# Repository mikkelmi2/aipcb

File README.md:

# aipcb

**A circuit board described as intent, compiled to KiCad.**

You write what the circuit *is* — in YAML. `aipcb` compiles it into real KiCad
schematics and boards, places, routes, pours, runs KiCad's own ERC and DRC on the
result, and can hand each pair to a field solver. Every problem points back at the
source line that caused it, and your KiCad edits survive the next build.

That is `examples/pcie-sata`, bundled here — a PCIe x1 card, four-port SATA, eleven
controlled-impedance pairs, four layers. Every image below is generated from it by
[`tools/make_images.py`](tools/make_images.py).

## What fifteen milestones hardened

**Deterministic compilation.** The same YAML gives byte-identical KiCad files —
rebuild unchanged and the file is not even rewritten. Every UUID is derived from
the source, which is what maps each element back to the line that asked for it.

**Verification you can trust.** ERC and DRC are run by KiCad itself, never
reimplemented, and come back as source-referenced diagnostics. Three invariants
guard the tool that produces them: `check` is a function of its source, no two
nets' copper may overlap, no simulation slice may be built with unbonded copper or
an unreachable reference plane. Each was learnt from a real defect, and
[`docs/reports/`](docs/reports/) tells the stories.

**Schematic generation.** Sheets drawn by convention from what the source already
knows — what serves what, which rails go up — proven identical to the source
netlist pin for pin, and ERC-clean.

**Manual layout is first-class.** `preserve` carries your KiCad edits across
rebuilds, `sync-placement` writes parts you moved back into the source,
`routing: manual` marks a net as yours, and the Freerouting bridge checks what
another router sends back.

## Maturity at a glance

| | | |
|---|---|---|
| Source format, compilation, `check`, schematics | **stable** | [`format.md`](docs/format.md) |
| Manual layout — preserve, `sync-placement`, `routing: manual` | **stable** | [`workflows.md`](docs/workflows.md) |
| Part placement | **basic** — shelf-packed clusters, unoptimised on purpose | [`roadmap.md`](docs/roadmap.md#placement) |
| Autorouting | **beta** — finishes this corpus, has never met a board it did not design | [`topology.md`](docs/topology.md) |
| SI simulation | **beta** — physically valid on ten of eleven links | [`m13.md`](docs/reports/m13.md) |
| Freerouting bridge | **new** — landed in M14e | [`external-routers.md`](docs/external-routers.md) |

## What beta means here

**The autorouter** finishes the corpus: `examples/pcie-sata` comes back **90 of 90
connections routed, 12 of 12 pairs coupled, 0 errors from KiCad's own DRC**, on
four layers. What it has not done is meet a board somebody else designed. The label
costs little: it **fails loudly**, naming each connection it could not finish
rather than leaving the board quietly short, and it is **optional** —
`routing: manual` and the Freerouting bridge take it out of the loop.

**SI simulation** extracts ten of the eleven flagship links physically; the
eleventh is reported unusable rather than plotted. It validates the layout you
declared, not the board a fabricator presses: it finds a pair routed too narrow, it
does not replace a test coupon, and it certifies compliance with nothing.

*Beta is a measurement, not a mood:* routing graduates once it has routed five
externally-contributed boards, passed a harder congestion stress example, and been
benchmarked against board size. The third of those is **done** — `aipcb bench`
records the whole corpus and CI diffs a subset on every change; routing cost grows
close to linearly in connections × triangulation size, and the numbers are in
[the M17 report](docs/reports/m17.md). The other two need a board this project did
not design. [The conditions in full](docs/roadmap.md#maturity-and-graduation).

## Source to fabrication, in six steps

### 1. Declare intent, not geometry

The width is *derived* from the impedance and the stackup — you never compute it:

```yaml
net_classes:
  pcie_tx:
    impedance_diff_ohm: 85    # the requirement; the trace width follows
    diff_pair_gap_mm: 0.15    # a manufacturing choice, so an input
    max_skew_mm: 0.127        # PCIe CEM r3.0 §4.7.7, for an add-in card
    reference: In1.Cu         # the plane the return current uses
```

### 2. It compiles to a schematic

### 3. Parts are placed

Mechanically-fixed parts anchor the board, everything else is placed relative to
what it serves, and the outline is checked against the card-edge footprint's own
`Edge.Cuts` rather than drawn twice.

### 4. And routed

A topological router negotiating congestion across four layers. Coupled pairs route
as one object — through the AC-coupling capacitors, across layer changes, at the
derived width.

### 5. The pairs are simulated

`aipcb simulate` slices each pair out of the routed board with its reference plane,
meshes it, runs openEMS.

The honest version of that picture: **six of the eleven pairs come back more than
10% from the impedance they declared**. That is the step doing its job: the
closed-form width says one thing, the field solver says how wrong it was.

### 6. And exported for fabrication — or for assembly

`aipcb export` writes Gerbers, drill files, a BOM and a placement file — the render
at the top of this page is KiCad's, from that output. `--assembly` adds what an
*assembler* needs on top of what a fabricator does: a bill of materials and a
centroid file in JLCPCB's or PCBWay's own columns, and a placement overlay drawn
from the centroid file itself, so the rotations can be looked at before anything is
ordered.

## You do the layout, if you want

| Mode | You do | aipcb does |
|---|---|---|
| **Full auto** | nothing | places, routes, pours, checks |
| **Hybrid** | draw the nets you care about, in KiCad | routes the rest *around* your copper, never through it, and checks all of it identically |
| **Fully manual** | all the copper | schematic, placement, pours, ERC/DRC, high-speed checks, export |

Hybrid is the one most people want. Mark a net or a whole class as yours:

```yaml
nets:
  PCIE_TXP: { class: pcie_tx, routing: manual }   # this one is mine
```

`aipcb check --json` then reports every net as `manual-routed`, `manual-pending`,
`auto-routed` or `handed-over`. `manual-pending` is the one that matters: a board
whose critical pairs are declared-and-not-yet-drawn looks finished to anything
counting unrouted connections, and this names it. Or hand the board to another
router — [Freerouting, headlessly](docs/external-routers.md).

## Quickstart

Python 3.12+ and **KiCad 9**, the backend rather than an optional extra: compiling
reads its stock libraries, and check, render and export shell out to `kicad-cli`.

```bash
git clone https://github.com/mikkelmi2/aipcb && cd aipcb
python3 -m venv .venv && .venv/bin/pip install -e .
.venv/bin/aipcb validate examples/usb-port/design.yaml
```

About 7 seconds on a warm pip cache, and out comes `ok: no problems found` with a
one-line summary. Now build it and open the result in KiCad:

```bash
.venv/bin/aipcb build examples/usb-port/design.yaml
kicad examples/usb-port/usb-port.kicad_pro
```

Then break it on purpose — change `diff_pair: USB_DP` to `USB_DPP` under
`nets: USB_DM:` — and validate again. Located, coded diagnostics rather than a
stack trace is what makes the loop work:

```
examples/usb-port/design.yaml:53:3: error[asymmetric-diff-pair]: net 'USB_DP'
names 'USB_DM' as its differential partner, but 'USB_DM' names USB_DPP
  at: nets.USB_DM.diff_pair
  hint: set `diff_pair: USB_DP` on 'USB_DM'
[... and error[unknown-diff-pair] for the net 'USB_DPP' that does not exist]

2 errors
```

`--json` gives the same thing machine-readably. [`docs/format.md`](docs/format.md)
is the reference for every key; [`docs/workflows.md`](docs/workflows.md) is how the
loop is used.

## What it does not do

**Not built.** Dense BGA escape, DDR fly-by topologies, HDI (blind and buried
vias), six or more layers, multi-sheet schematics, buses. Not "coming soon" —
absent, and a board needing them hands over rather than guesses. The class shown to
finish is the one above: small, high-speed-critical, two or four layers, and
[`docs/roadmap.md`](docs/roadmap.md) says which of the rest are wanted.

**No board from this repository has been fabricated yet.** When one has, this
paragraph will say so with pictures.

## Documentation

[`docs/README.md`](docs/README.md) is the map, and repeats the tiers above.

**This project was built milestone by milestone by AI agents, and the whole
engineering record is in the repository** — every specification, thirteen decision
records, and a delivery report per milestone measuring what actually landed. Start
at [`docs/reports/`](docs/reports/): written for someone who was not there, and
candid about what did not work.

Contributions are welcome — [`CONTRIBUTING.md`](CONTRIBUTING.md) says how. A board
this did not design is the most useful thing you can bring.

Apache-2.0. See [`LICENSE`](LICENSE) and [`NOTICE`](NOTICE).

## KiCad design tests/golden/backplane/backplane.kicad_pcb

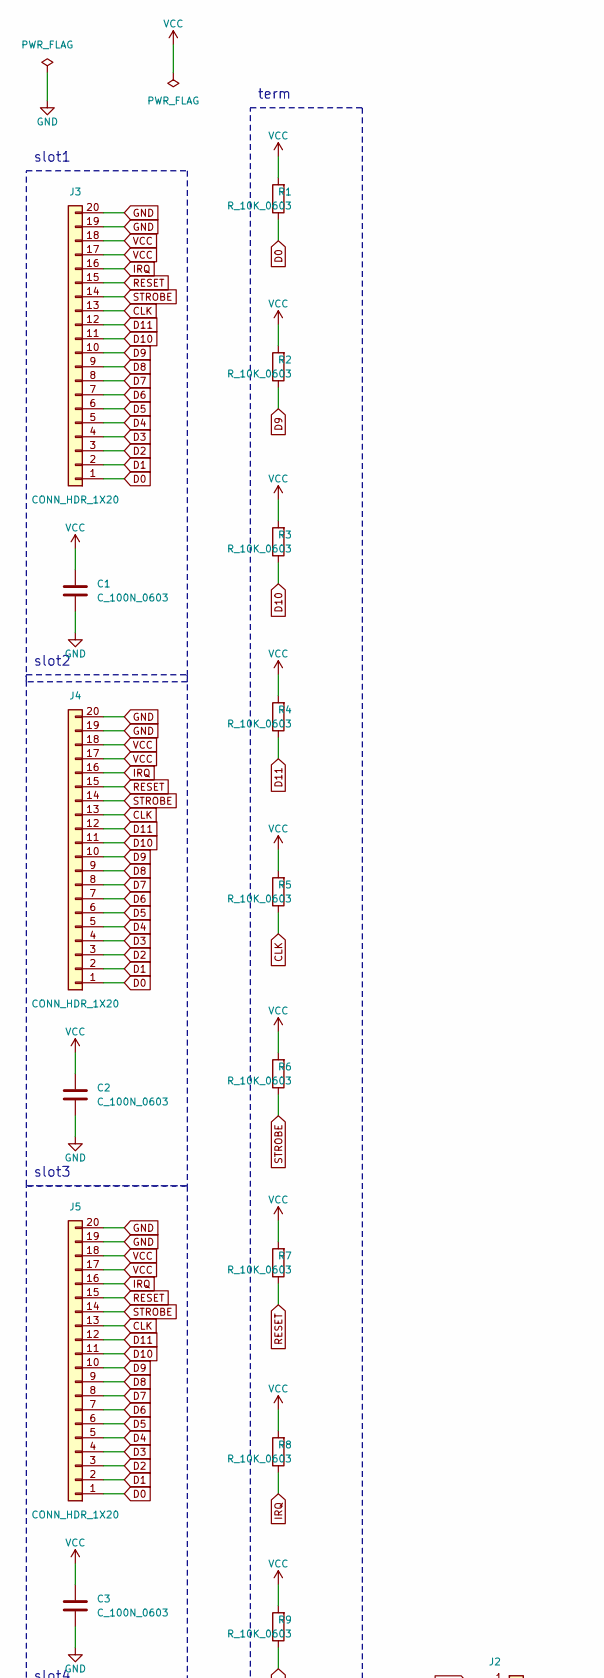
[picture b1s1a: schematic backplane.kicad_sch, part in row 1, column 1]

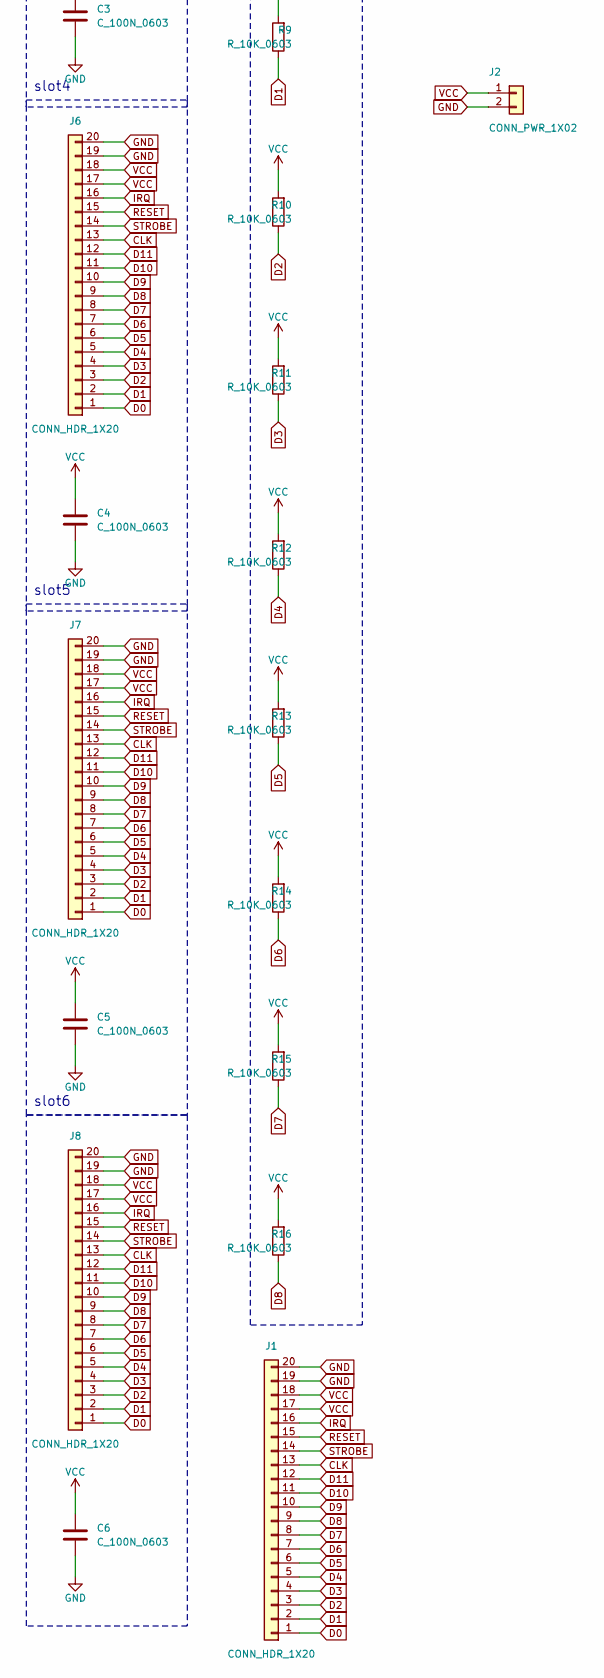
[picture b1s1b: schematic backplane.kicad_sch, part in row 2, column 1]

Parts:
C1, C2, C3, C4, C5, C6: C_100N_0603; C_0603_1608Metric
J1, J3, J4, J5, J6, J7, J8: CONN_HDR_1X20; PinHeader_1x20_P2.54mm_Vertical
J2: CONN_PWR_1X02; PinHeader_1x02_P2.54mm_Vertical
R1, R2, R3, R4, R5, R6, R7, R8, R9, R10, R11, R12, R13, R14, R15, R16: R_10K_0603; R_0603_1608Metric

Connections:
CLK: J1.13, J3.13, J4.13, J5.13, J6.13, J7.13, J8.13, R5.1
D0: J1.1, J3.1, J4.1, J5.1, J6.1, J7.1, J8.1, R1.1
D1: J1.2, J3.2, J4.2, J5.2, J6.2, J7.2, J8.2, R9.1
D2: J1.3, J3.3, J4.3, J5.3, J6.3, J7.3, J8.3, R10.1
D3: J1.4, J3.4, J4.4, J5.4, J6.4, J7.4, J8.4, R11.1
D4: J1.5, J3.5, J4.5, J5.5, J6.5, J7.5, J8.5, R12.1
D5: J1.6, J3.6, J4.6, J5.6, J6.6, J7.6, J8.6, R13.1
D6: J1.7, J3.7, J4.7, J5.7, J6.7, J7.7, J8.7, R14.1
D7: J1.8, J3.8, J4.8, J5.8, J6.8, J7.8, J8.8, R15.1
D8: J1.9, J3.9, J4.9, J5.9, J6.9, J7.9, J8.9, R16.1
D9: J1.10, J3.10, J4.10, J5.10, J6.10, J7.10, J8.10, R2.1
D10: J1.11, J3.11, J4.11, J5.11, J6.11, J7.11, J8.11, R3.1
D11: J1.12, J3.12, J4.12, J5.12, J6.12, J7.12, J8.12, R4.1
GND: C1.2, C2.2, C3.2, C4.2, C5.2, C6.2, J1.19, J1.20, J2.2, J3.19, J3.20, J4.19, J4.20, J5.19, J5.20, J6.19, J6.20, J7.19, J7.20, J8.19, J8.20
IRQ: J1.16, J3.16, J4.16, J5.16, J6.16, J7.16, J8.16, R8.1
RESET: J1.15, J3.15, J4.15, J5.15, J6.15, J7.15, J8.15, R7.1
STROBE: J1.14, J3.14, J4.14, J5.14, J6.14, J7.14, J8.14, R6.1
VCC: C1.1, C2.1, C3.1, C4.1, C5.1, C6.1, J1.17, J1.18, J2.1, J3.17, J3.18, J4.17, J4.18, J5.17, J5.18, J6.17, J6.18, J7.17, J7.18, J8.17, J8.18, R1.2, R2.2, R3.2, R4.2, R5.2, R6.2, R7.2, R8.2, R9.2, R10.2, R11.2, R12.2, R13.2, R14.2, R15.2, R16.2

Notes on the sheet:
slot1
slot2
slot3
slot4
slot5
slot6
term

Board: 4 copper layers, 30 parts (0 on the bottom side), 18 nets, no tracks yet.

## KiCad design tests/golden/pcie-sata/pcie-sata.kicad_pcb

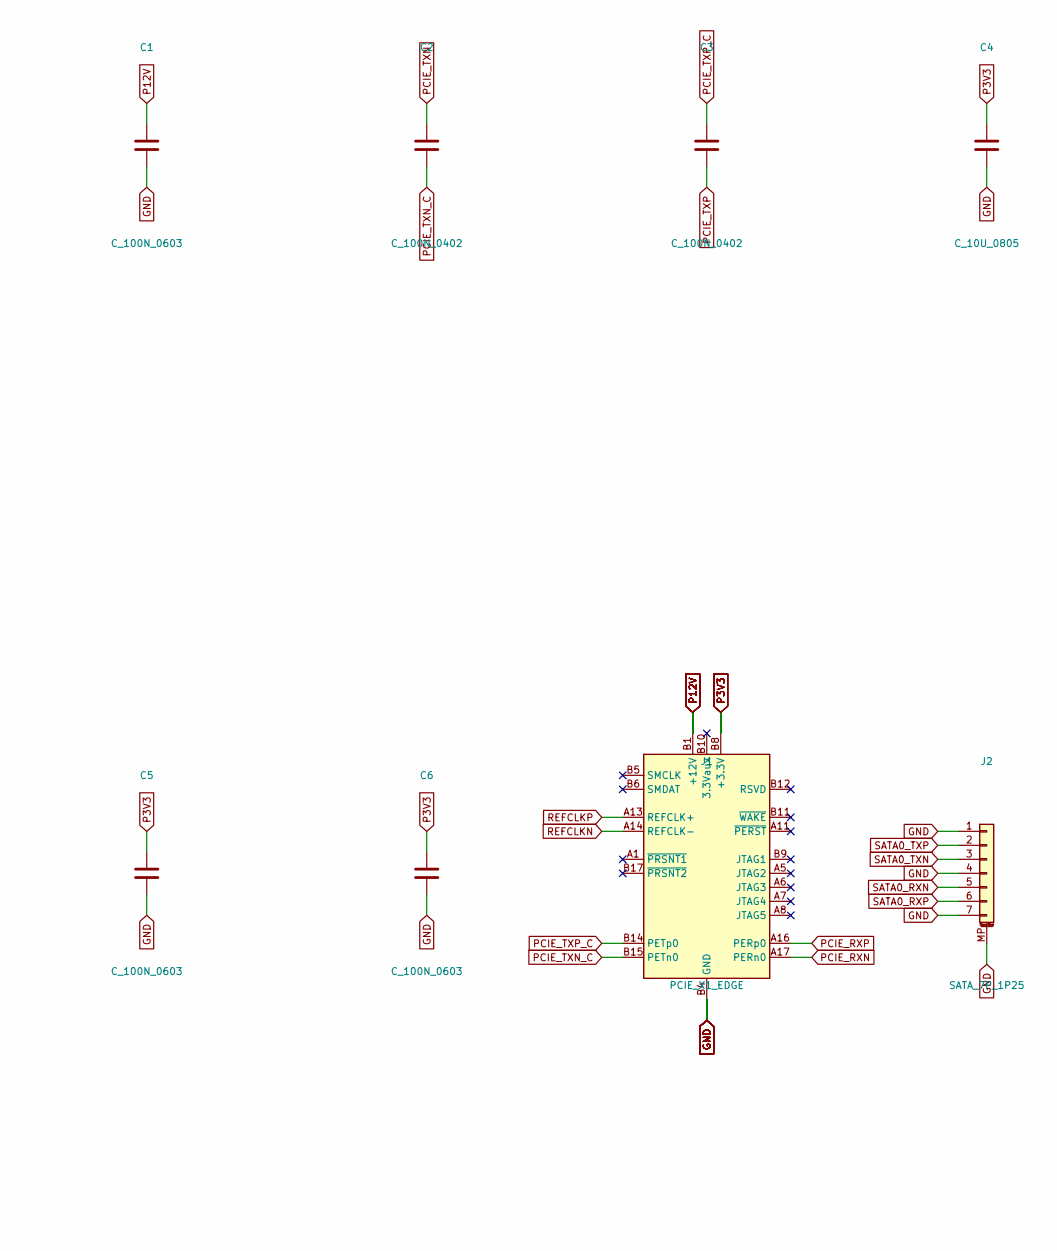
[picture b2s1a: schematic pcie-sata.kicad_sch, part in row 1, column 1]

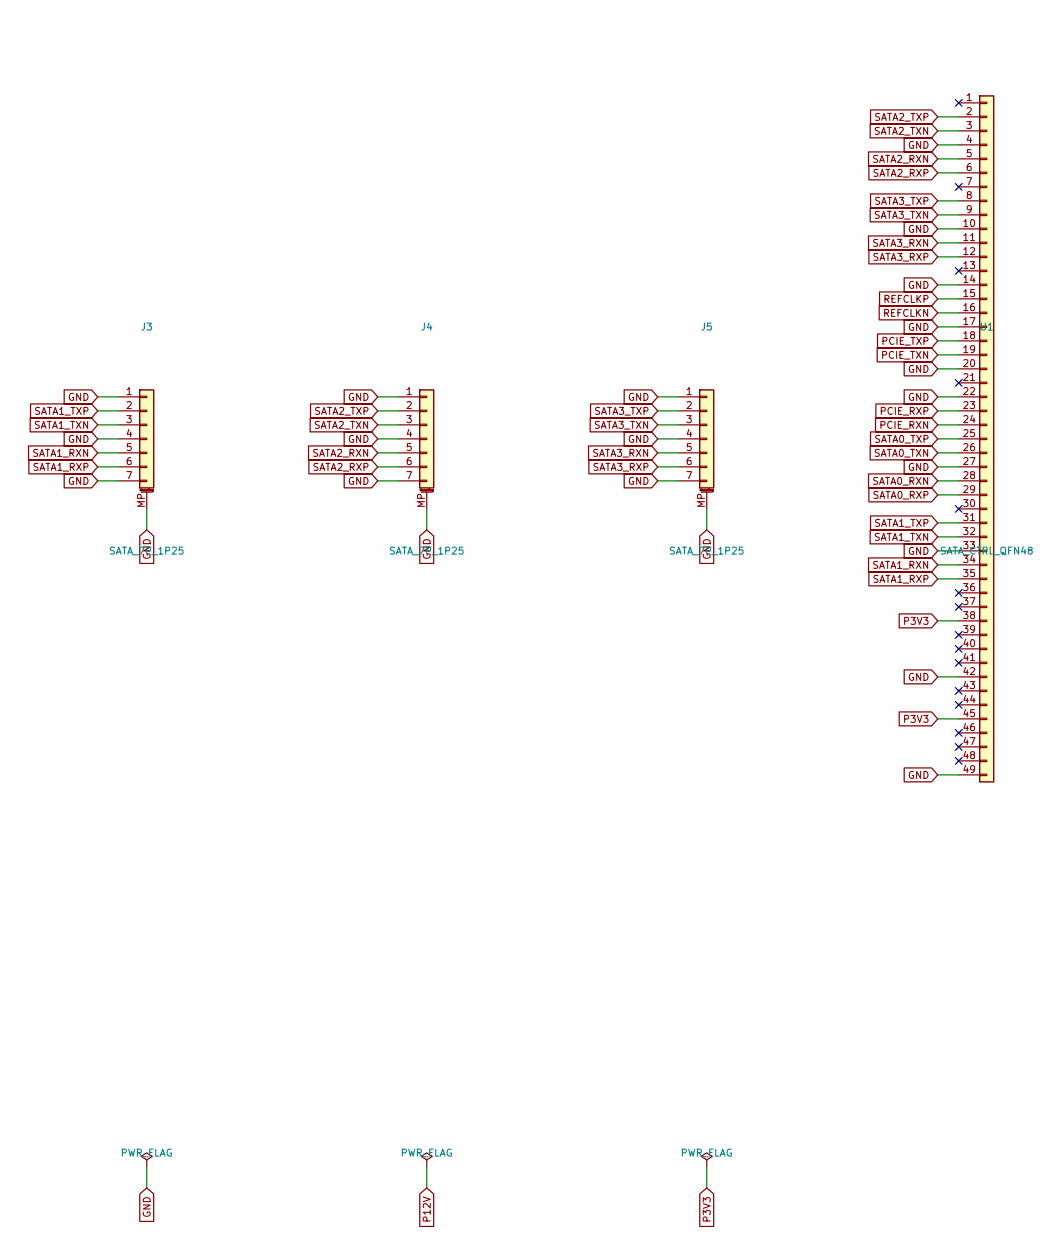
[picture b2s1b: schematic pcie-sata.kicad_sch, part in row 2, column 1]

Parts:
C1, C5, C6: C_100N_0603; C_0603_1608Metric
C2, C3: C_100N_0402; C_0402_1005Metric
C4: C_10U_0805; C_0805_2012Metric
J1: PCIE_X1_EDGE; BUS_PCIexpress_x1
J2, J3, J4, J5: SATA_7P_1P25; JST_GH_SM07B-GHS-TB_1x07-1MP_P1.25mm_Horizontal
U1: SATA_CTRL_QFN48; QFN-48-1EP_7x7mm_P0.5mm_EP5.15x5.15mm

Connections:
GND: C1.2, C4.2, C5.2, C6.2, J1.A4 (GND), J1.A12 (GND), J1.A15 (GND), J1.A18 (GND), J1.B4 (GND), J1.B7 (GND), J1.B13 (GND), J1.B16 (GND), J1.B18 (GND), J2.1, J2.4, J2.7, J2.MP (MountPin), J3.1, J3.4, J3.7, J3.MP (MountPin), J4.1, J4.4, J4.7, J4.MP (MountPin), J5.1, J5.4, J5.7, J5.MP (MountPin), U1.4, U1.10, U1.14, U1.17, U1.20, U1.22, U1.27, U1.33, U1.42, U1.49
P3V3: C4.1, C5.1, C6.1, J1.A9 (+3.3V), J1.A10 (+3.3V), J1.B8 (+3.3V), U1.38, U1.45
P12V: C1.1, J1.A2 (+12V), J1.A3 (+12V), J1.B1 (+12V), J1.B2 (+12V), J1.B3 (+12V)
PCIE_RXN: J1.A17 (PERn0), U1.24
PCIE_RXP: J1.A16 (PERp0), U1.23
PCIE_TXN: C2.1, U1.19
PCIE_TXN_C: C2.2, J1.B15 (PETn0)
PCIE_TXP: C3.2, U1.18
PCIE_TXP_C: C3.1, J1.B14 (PETp0)
REFCLKN: J1.A14 (REFCLK-), U1.16
REFCLKP: J1.A13 (REFCLK+), U1.15
SATA0_RXN: J2.5, U1.28
SATA0_RXP: J2.6, U1.29
SATA0_TXN: J2.3, U1.26
SATA0_TXP: J2.2, U1.25
SATA1_RXN: J3.5, U1.34
SATA1_RXP: J3.6, U1.35
SATA1_TXN: J3.3, U1.32
SATA1_TXP: J3.2, U1.31
SATA2_RXN: J4.5, U1.5
SATA2_RXP: J4.6, U1.6
SATA2_TXN: J4.3, U1.3
SATA2_TXP: J4.2, U1.2
SATA3_RXN: J5.5, U1.11
SATA3_RXP: J5.6, U1.12
SATA3_TXN: J5.3, U1.9
SATA3_TXP: J5.2, U1.8

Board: 4 copper layers, 12 parts (0 on the bottom side), 27 nets, no tracks yet.

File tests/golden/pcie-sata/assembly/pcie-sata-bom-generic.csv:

Designators,Quantity,Value,Footprint,Package,Assembly,Manufacturer,MPN,Supplier Refs,Description
"C1,C5,C6",3,100n,Capacitor_SMD:C_0603_1608Metric,C_0603_1608Metric,smt,,,,"100 nF X7R ceramic capacitor, 0603, 50 V"
"C2,C3",2,100n,Capacitor_SMD:C_0402_1005Metric,C_0402_1005Metric,smt,,,,"100 nF X7R ceramic capacitor, 0402, 16 V -- the AC-coupling part for a PCIe transmit pair, small enough that the pair barely notices it."
C4,1,10u,Capacitor_SMD:C_0805_2012Metric,C_0805_2012Metric,smt,,,,"10 uF X5R ceramic capacitor, 0805, 16 V"
"J2,J3,J4,J5",4,SATA data,Connector_JST:JST_GH_SM07B-GHS-TB_1x07-1MP_P1.25mm_Horizontal,JST_GH_SM07B-GHS-TB_1x07-1MP_P1.25mm_Horizontal,smt,JST,SM07B-GHS-TB,,"7-way 1.25 mm side-entry connector standing in for a SATA data receptacle -- same contact count and very nearly the same pitch. Two shell pads, both numbered MP, which is the same shared-pad-number case as a USB receptacle's shield tabs."
U1,1,SATA-CTRL-48,Package_DFN_QFN:QFN-48-1EP_7x7mm_P0.5mm_EP5.15x5.15mm,QFN-48-1EP_7x7mm_P0.5mm_EP5.15x5.15mm,smt,,,,"A PCIe x1 to 4-port SATA bridge controller, ASM1064 class, in a 48-pin QFN with an exposed pad. See the note at the top of this file about the symbol."

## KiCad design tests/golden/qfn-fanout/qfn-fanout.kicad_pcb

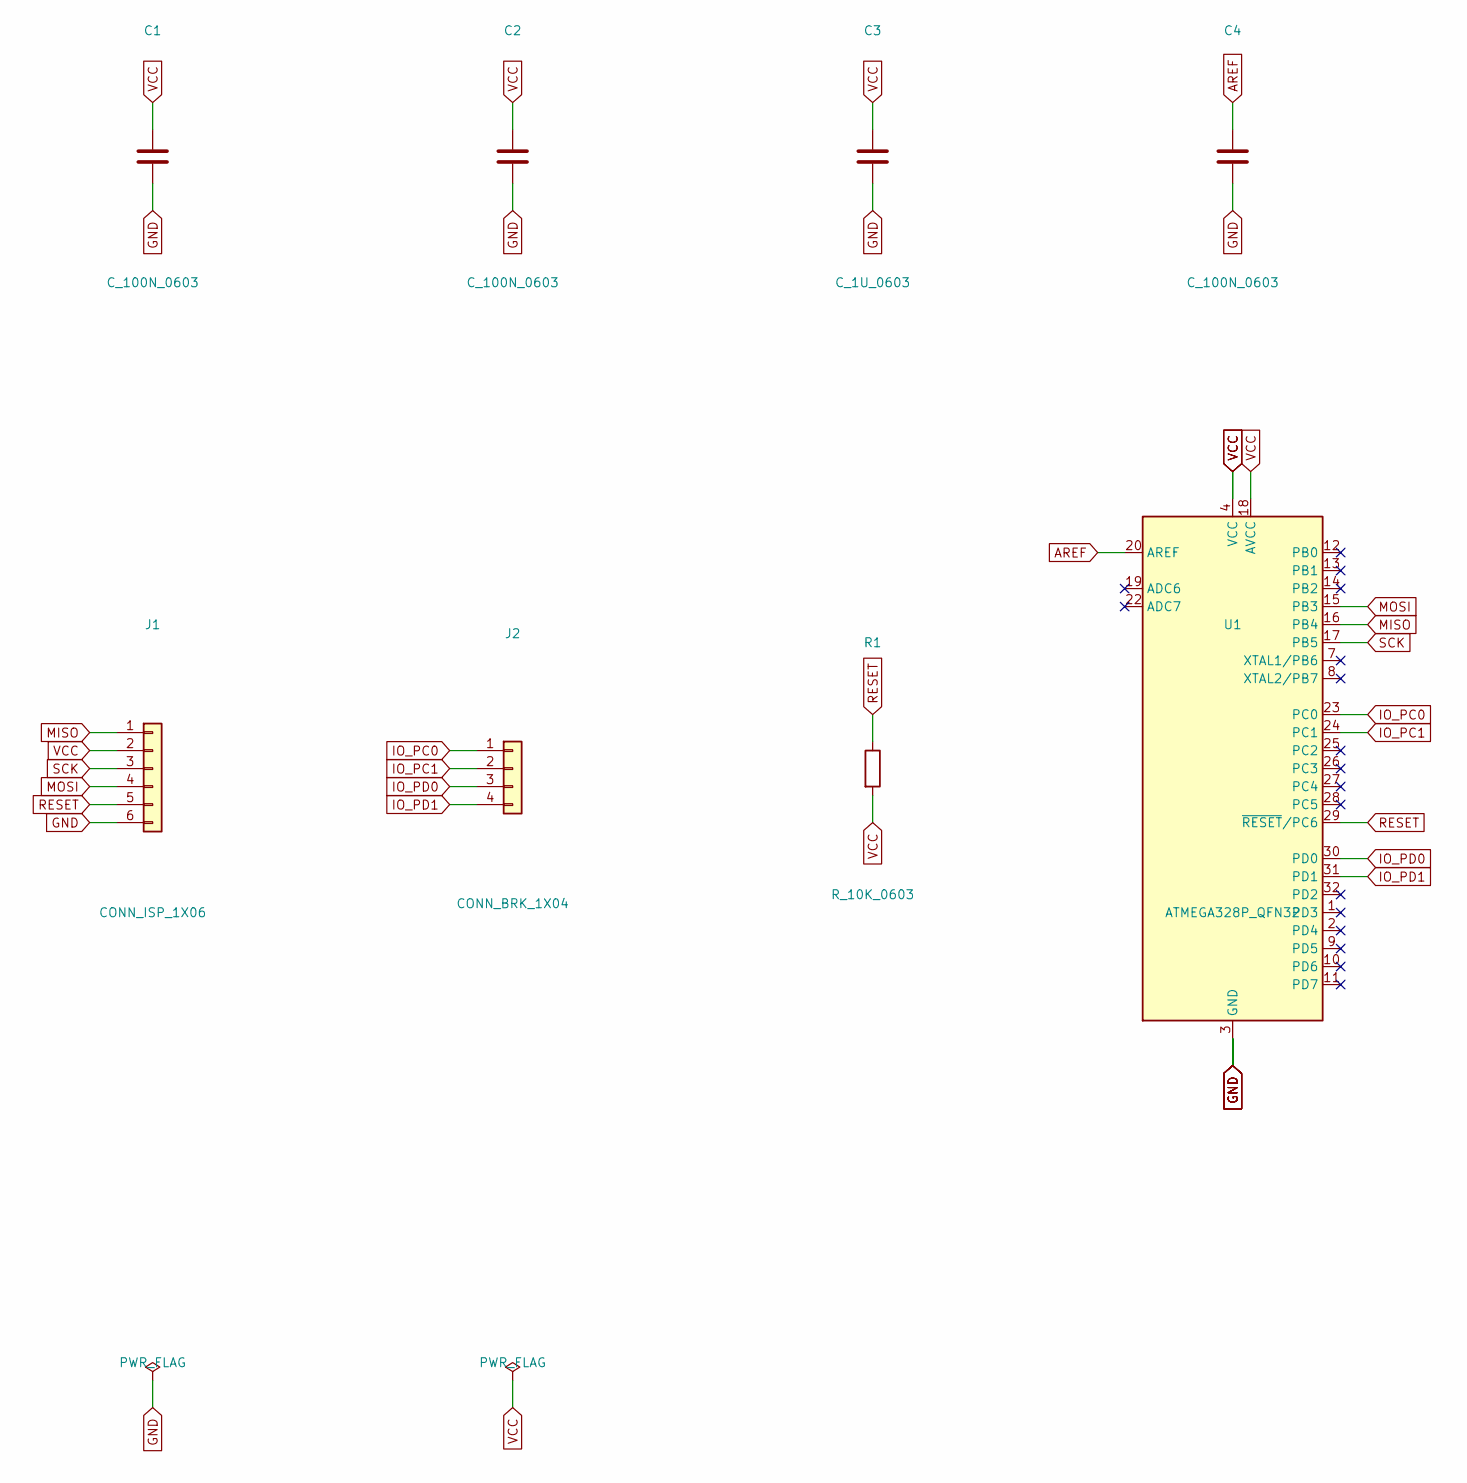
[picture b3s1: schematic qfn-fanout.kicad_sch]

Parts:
C1, C2, C4: C_100N_0603; C_0603_1608Metric
C3: C_1U_0603; C_0603_1608Metric
J1: CONN_ISP_1X06; PinHeader_1x06_P2.54mm_Vertical
J2: CONN_BRK_1X04; PinHeader_1x04_P2.54mm_Vertical
R1: R_10K_0603; R_0603_1608Metric
U1: ATMEGA328P_QFN32; QFN-32-1EP_5x5mm_P0.5mm_EP3.1x3.1mm

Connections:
AREF: C4.1, U1.20 (AREF)
GND: C1.2, C2.2, C3.2, C4.2, J1.6, U1.3 (GND), U1.5 (GND), U1.21 (GND), U1.33 (GND)
IO_PC0: J2.1, U1.23 (PC0)
IO_PC1: J2.2, U1.24 (PC1)
IO_PD0: J2.3, U1.30 (PD0)
IO_PD1: J2.4, U1.31 (PD1)
MISO: J1.1, U1.16 (PB4)
MOSI: J1.4, U1.15 (PB3)
RESET: J1.5, R1.1, U1.29 (~RESET/PC6)
SCK: J1.3, U1.17 (PB5)
VCC: C1.1, C2.1, C3.1, J1.2, R1.2, U1.4 (VCC), U1.6 (VCC), U1.18 (AVCC)

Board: 2 copper layers, 8 parts (0 on the bottom side), 11 nets, no tracks yet.

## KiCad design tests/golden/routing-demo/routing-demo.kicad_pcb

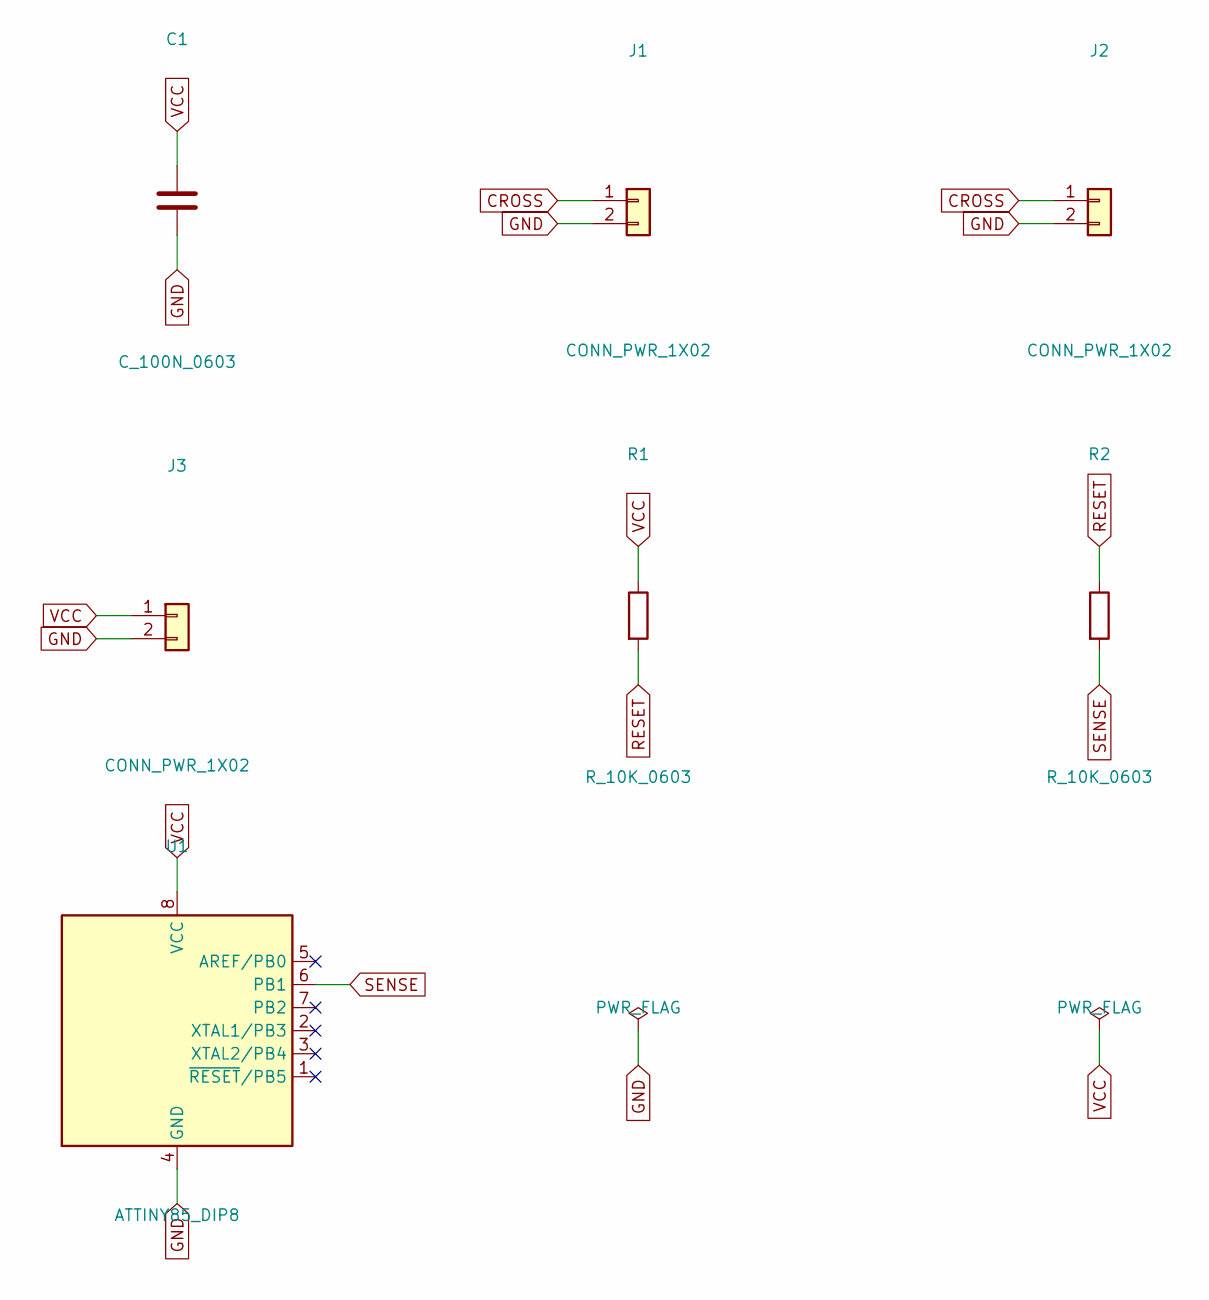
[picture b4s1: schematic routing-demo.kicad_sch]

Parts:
C1: C_100N_0603; C_0603_1608Metric
J1, J2, J3: CONN_PWR_1X02; PinHeader_1x02_P2.54mm_Vertical
R1, R2: R_10K_0603; R_0603_1608Metric
U1: ATTINY85_DIP8; DIP-8_W7.62mm

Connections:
CROSS: J1.1, J2.1
GND: C1.2, J1.2, J2.2, J3.2, U1.4 (GND)
RESET: R1.2, R2.1
SENSE: R2.2, U1.6 (PB1)
VCC: C1.1, J3.1, R1.1, U1.8 (VCC)

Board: 2 copper layers, 7 parts (0 on the bottom side), 5 nets, no tracks yet.

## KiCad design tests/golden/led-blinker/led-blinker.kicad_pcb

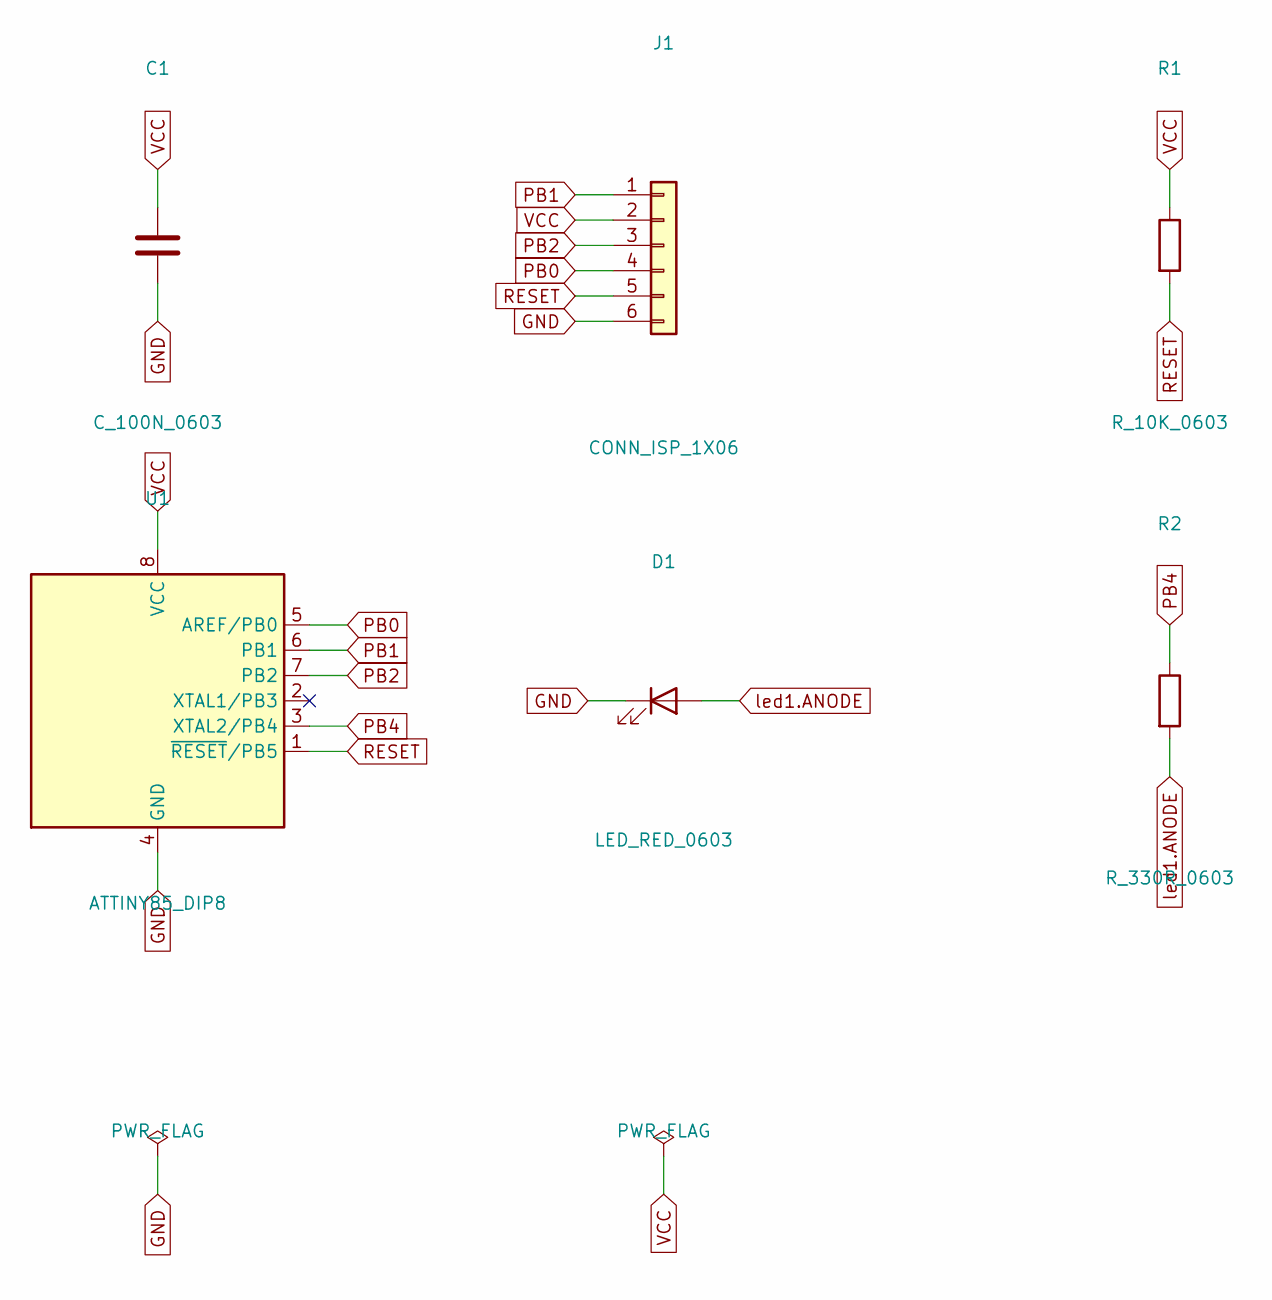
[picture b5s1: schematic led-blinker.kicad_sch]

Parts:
C1: C_100N_0603; C_0603_1608Metric
D1: LED_RED_0603; LED_0603_1608Metric
J1: CONN_ISP_1X06; PinHeader_1x06_P2.54mm_Vertical
R1: R_10K_0603; R_0603_1608Metric
R2: R_330R_0603; R_0603_1608Metric
U1: ATTINY85_DIP8; DIP-8_W7.62mm

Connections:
GND: C1.2, D1.1 (K), J1.6, U1.4 (GND)
PB0: J1.4, U1.5 (AREF/PB0)
PB1: J1.1, U1.6 (PB1)
PB2: J1.3, U1.7 (PB2)
PB4: R2.1, U1.3 (XTAL2/PB4)
RESET: J1.5, R1.2, U1.1 (~RESET/PB5)
VCC: C1.1, J1.2, R1.1, U1.8 (VCC)
led1.ANODE: D1.2 (A), R2.2

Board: 2 copper layers, 6 parts (0 on the bottom side), 8 nets, no tracks yet.

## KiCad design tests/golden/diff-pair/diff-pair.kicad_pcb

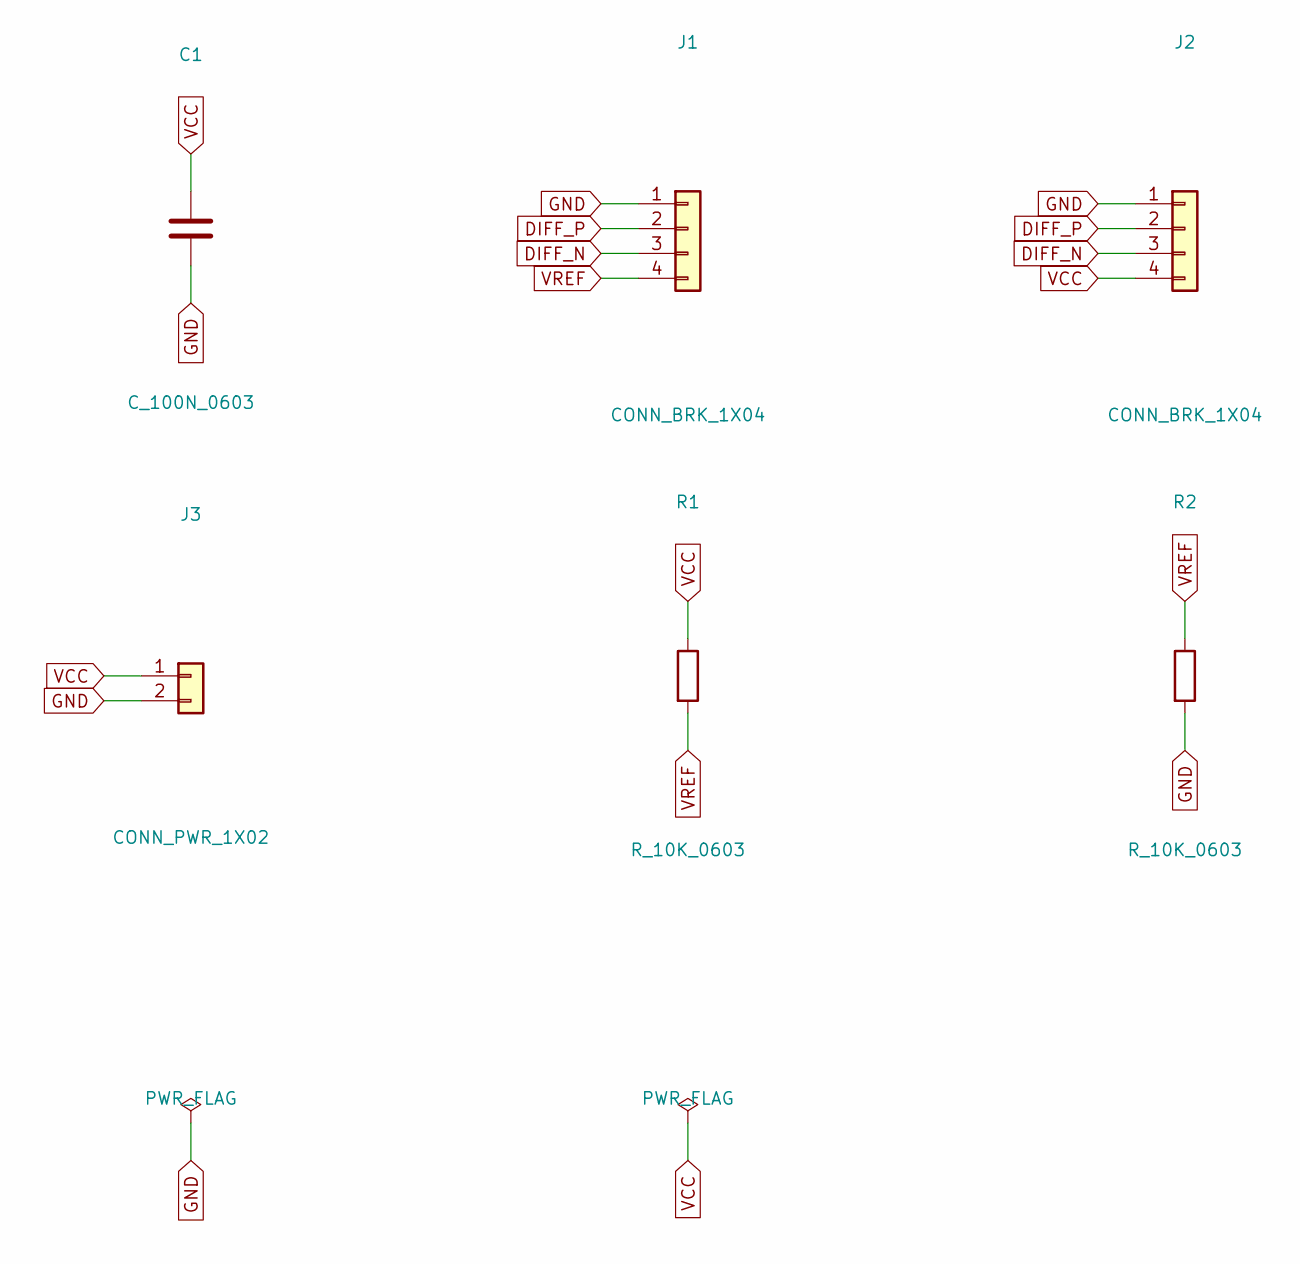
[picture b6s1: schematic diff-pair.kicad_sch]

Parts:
C1: C_100N_0603; C_0603_1608Metric
J1, J2: CONN_BRK_1X04; PinHeader_1x04_P2.54mm_Vertical
J3: CONN_PWR_1X02; PinHeader_1x02_P2.54mm_Vertical
R1, R2: R_10K_0603; R_0603_1608Metric

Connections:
DIFF_N: J1.3, J2.3
DIFF_P: J1.2, J2.2
GND: C1.2, J1.1, J2.1, J3.2, R2.2
VCC: C1.1, J2.4, J3.1, R1.1
VREF: J1.4, R1.2, R2.1

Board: 2 copper layers, 6 parts (0 on the bottom side), 5 nets, no tracks yet.

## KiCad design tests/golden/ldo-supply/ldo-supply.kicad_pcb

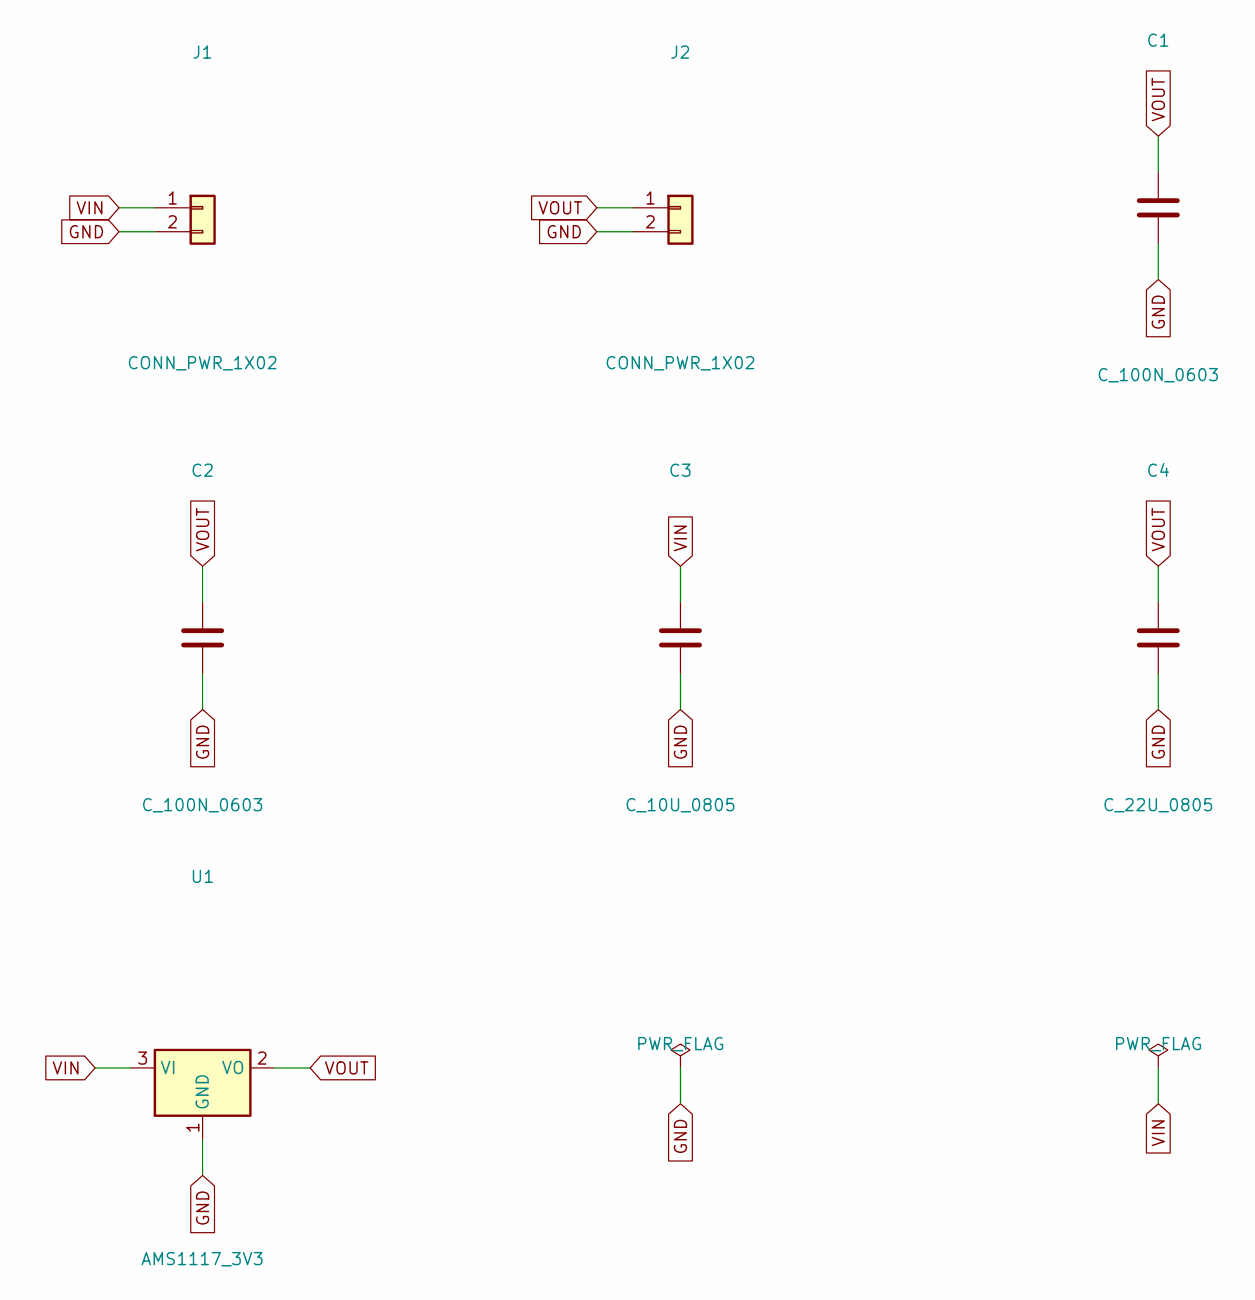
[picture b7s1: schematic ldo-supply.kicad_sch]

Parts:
C1, C2: C_100N_0603; C_0603_1608Metric
C3: C_10U_0805; C_0805_2012Metric
C4: C_22U_0805; C_0805_2012Metric
J1, J2: CONN_PWR_1X02; PinHeader_1x02_P2.54mm_Vertical
U1: AMS1117_3V3; SOT-223-3_TabPin2

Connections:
GND: C1.2, C2.2, C3.2, C4.2, J1.2, J2.2, U1.1 (GND)
VIN: C3.1, J1.1, U1.3 (VI)
VOUT: C1.1, C2.1, C4.1, J2.1, U1.2 (VO)

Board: 2 copper layers, 7 parts (0 on the bottom side), 3 nets, no tracks yet.

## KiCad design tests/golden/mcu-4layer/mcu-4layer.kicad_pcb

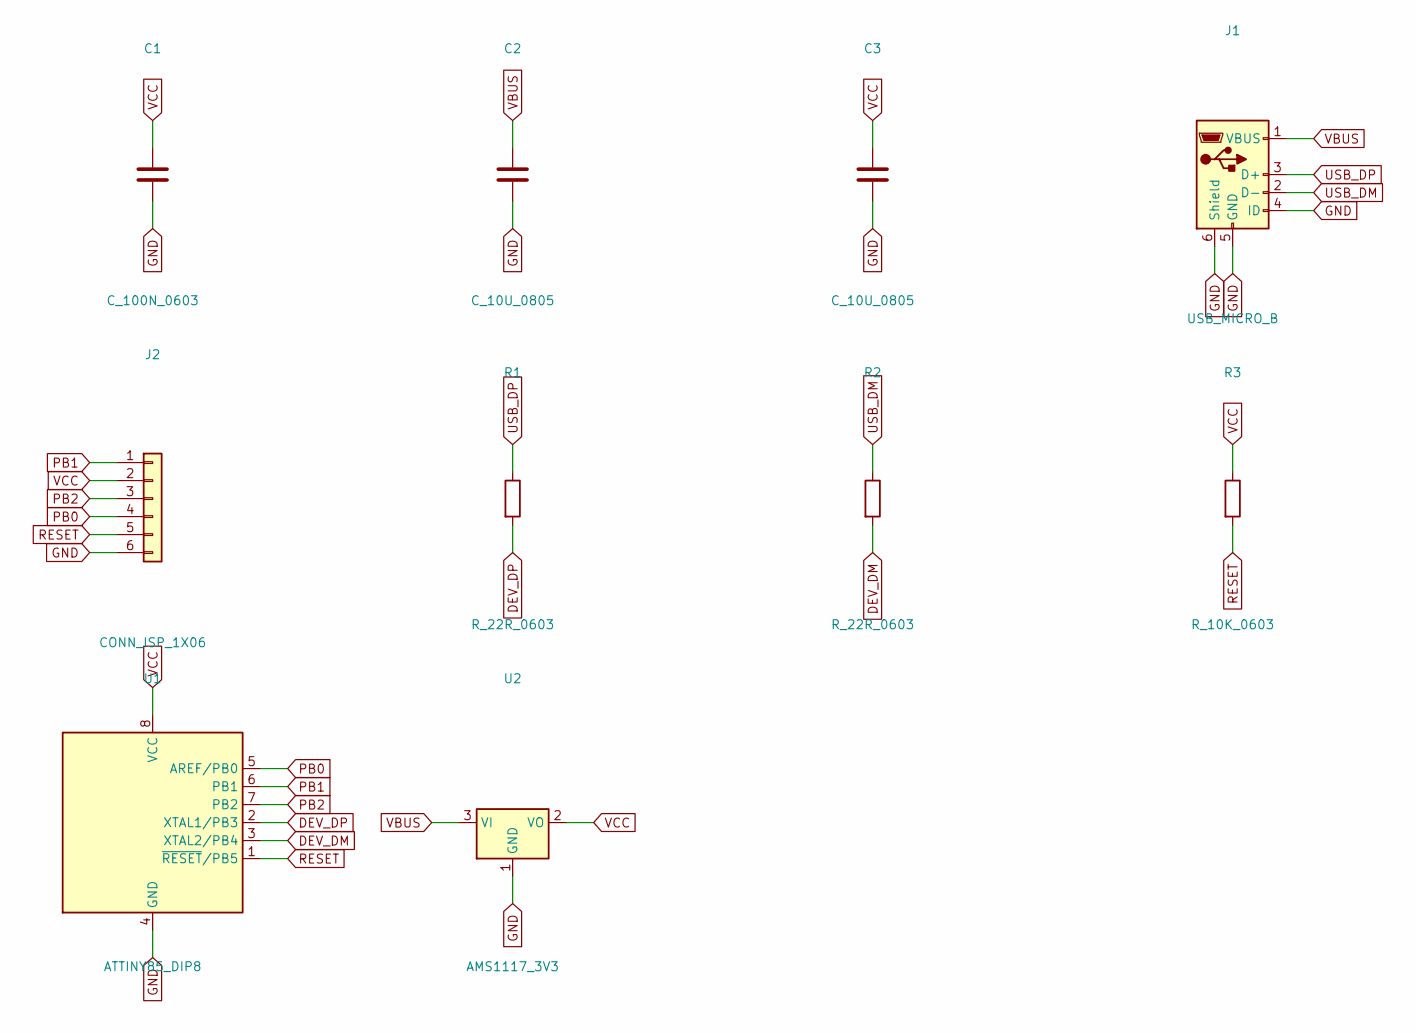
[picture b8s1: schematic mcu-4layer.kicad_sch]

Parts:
C1: C_100N_0603; C_0603_1608Metric
C2, C3: C_10U_0805; C_0805_2012Metric
J1: USB_MICRO_B; USB_Micro-B_Amphenol_10103594-0001LF_Horizontal
J2: CONN_ISP_1X06; PinHeader_1x06_P2.54mm_Vertical
R1, R2: R_22R_0603; R_0603_1608Metric
R3: R_10K_0603; R_0603_1608Metric
U1: ATTINY85_DIP8; DIP-8_W7.62mm
U2: AMS1117_3V3; SOT-223-3_TabPin2

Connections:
DEV_DM: R2.2, U1.3 (XTAL2/PB4)
DEV_DP: R1.2, U1.2 (XTAL1/PB3)
GND: C1.2, C2.2, C3.2, J1.4 (ID), J1.5 (GND), J1.6 (Shield), J2.6, U1.4 (GND), U2.1 (GND)
PB0: J2.4, U1.5 (AREF/PB0)
PB1: J2.1, U1.6 (PB1)
PB2: J2.3, U1.7 (PB2)
RESET: J2.5, R3.2, U1.1 (~RESET/PB5)
USB_DM: J1.2 (D-), R2.1
USB_DP: J1.3 (D+), R1.1
VBUS: C2.1, J1.1 (VBUS), U2.3 (VI)
VCC: C1.1, C3.1, J2.2, R3.1, U1.8 (VCC), U2.2 (VO)

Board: 4 copper layers, 10 parts (0 on the bottom side), 11 nets, no tracks yet.
